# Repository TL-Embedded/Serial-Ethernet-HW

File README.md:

# Serial-Ethernet-HW

This is an Ethernet to Serial adaptor.
See [Serial-Ethernet-FW](https://github.com/TL-Embedded/Serial-Ethernet-FW) for the firmware project.

The hardware is done using KiCad, and uses my component library found here: [KiCadLib](https://github.com/Lambosaurus/KicadLib)

The processor is a STM32G061.

# Ethernet
The ethernet is managed by a SPI attached W5500. The ethernet is capable of 10/100 speeds.

# Serial
The serial is a TTL level serial targeted at certain test equipment. Series resistance is used to tolerate both 3V3 and 5V0 devices.

**This is not compatible with RS232 level serial**

# Power
The device is powered from 5V. This can be supplied via:
 * USB Connector
 * Debug connector
 * DB9 pin 1 (omit L2 if this is not desired)

# Debugging
The debugging connector is a TC2050 compatible footprint. See the [SWD-UART_CTX-10](https://github.com/TL-Embedded/SWD-UART-CTX-10) project for the adaptor board.

This can be used to:
 * Connect to the STM32 via STLINK
 * Supply 5V
 * Connect a UART

The debugging connector has no input/output protection - so take care not to supply power or UART when the DB9 is connected.

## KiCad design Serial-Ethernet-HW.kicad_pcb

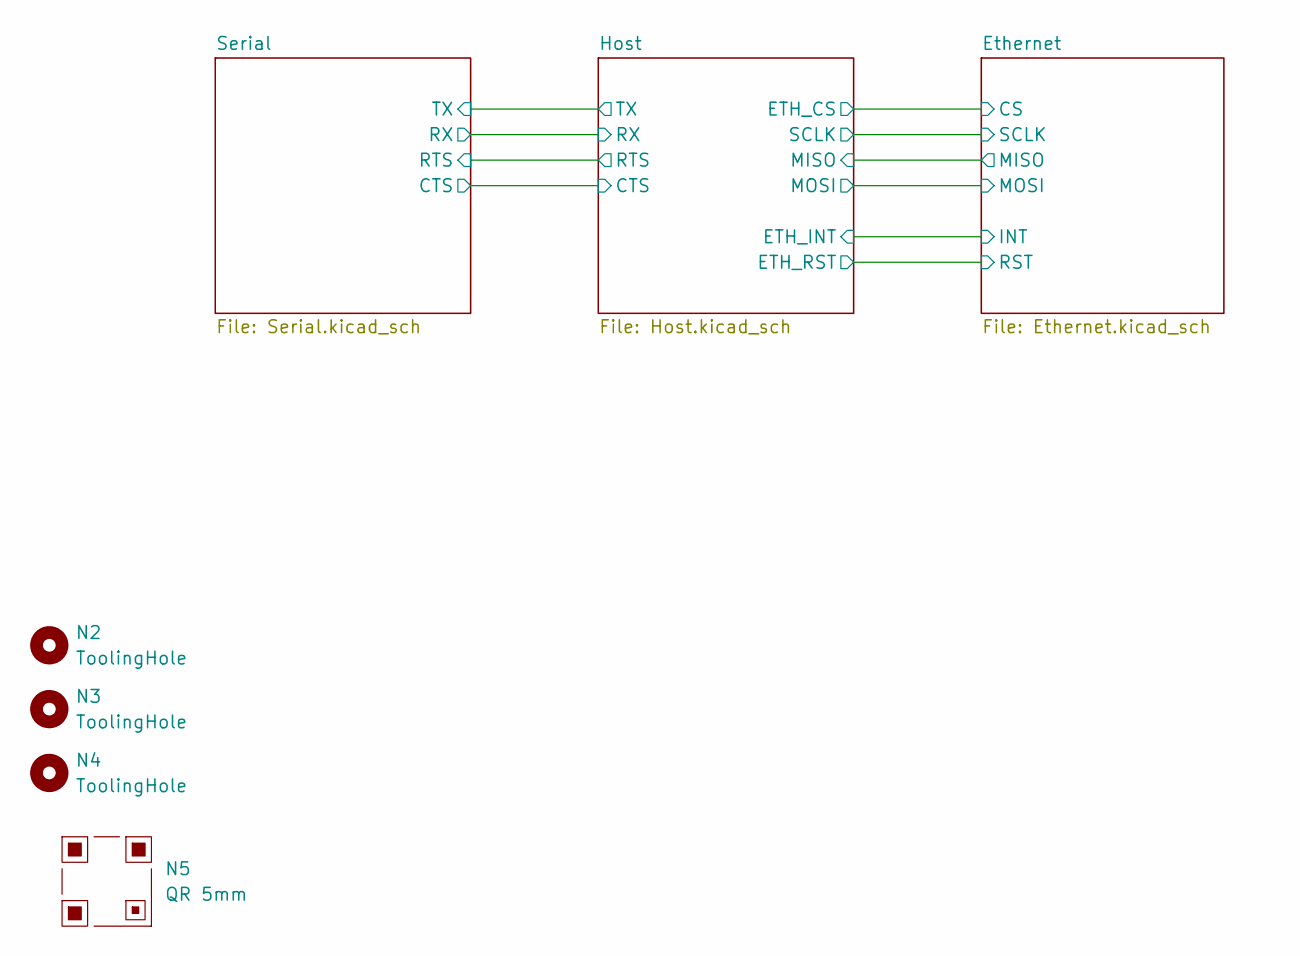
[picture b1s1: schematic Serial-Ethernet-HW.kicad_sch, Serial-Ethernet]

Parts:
N2, N3, N4: ToolingHole; ToolingHole_1mm
N5: QR 5mm; QR_5mm_JLC

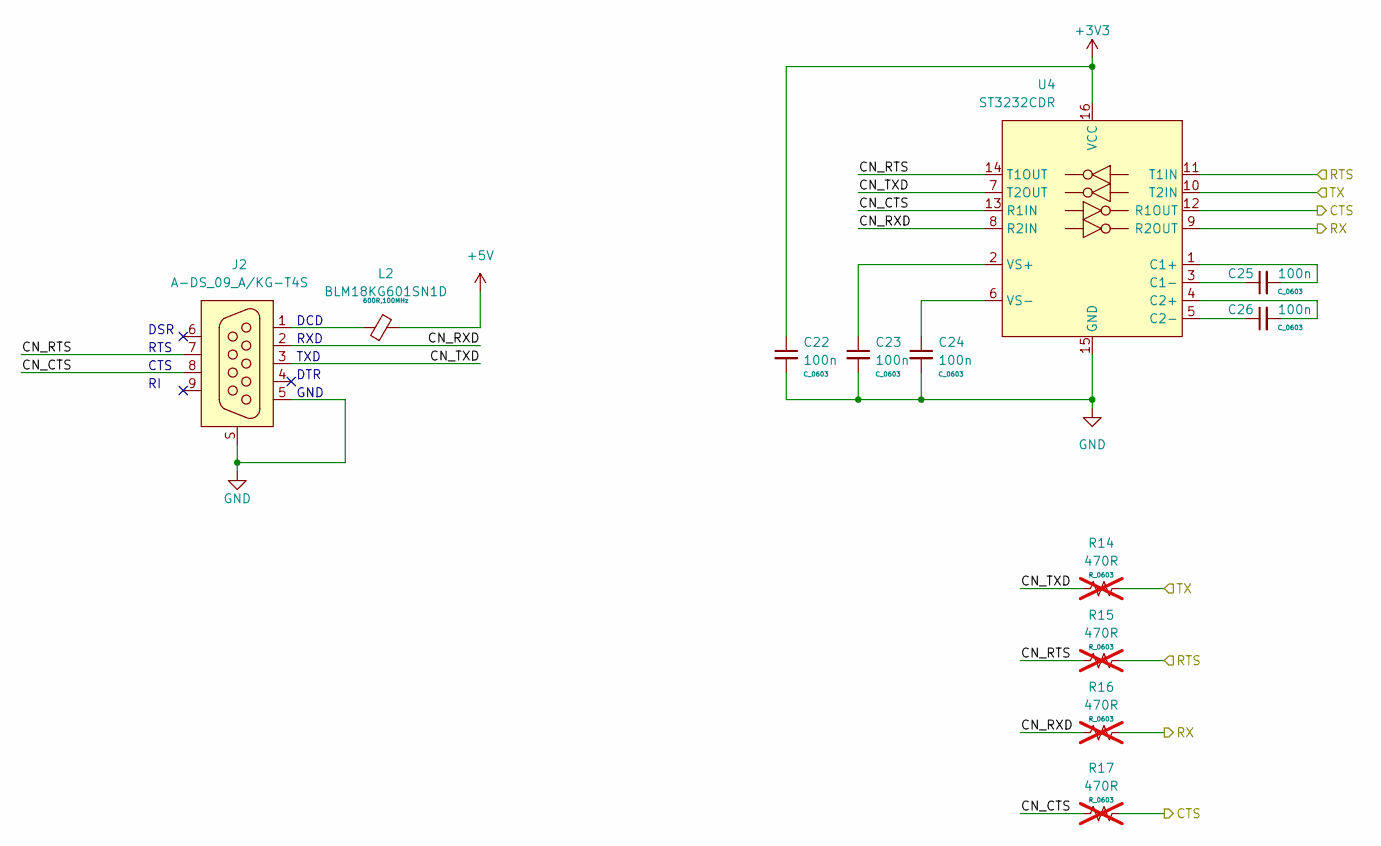
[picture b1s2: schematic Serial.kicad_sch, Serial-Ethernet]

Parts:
C22, C23, C24, C25, C26: 100n; C_0603
J2: A-DS_09_A/KG-T4S; DSUB09_Male_Horizontal
L2: BLM18KG601SN1D; FB_0603
R14, R15, R16, R17: 470R; R_0603; not fitted
U4: ST3232CDR; SOIC_16

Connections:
+3V3: C22.1, U4.16 (VCC); also elsewhere on the board
+5V: L2.2; also elsewhere on the board
/Host/CTS: R17.2, U4.12 (R1OUT); also elsewhere on the board
/Host/RTS: R15.2, U4.11 (T1IN); also elsewhere on the board
/Host/UART_RX: R16.2, U4.9 (R2OUT); also elsewhere on the board
/Host/UART_TX: R14.2, U4.10 (T2IN); also elsewhere on the board
/Serial/CN_CTS: J2.8, R17.1, U4.13 (R1IN)
/Serial/CN_RTS: J2.7, R15.1, U4.14 (T1OUT)
/Serial/CN_RXD: J2.2, R16.1, U4.8 (R2IN)
/Serial/CN_TXD: J2.3, R14.1, U4.7 (T2OUT)
GND: C22.2, C23.2, C24.2, J2.5, J2.S, U4.15 (GND); also elsewhere on the board
unnamed: J2.1, L2.1
unnamed: C25.2, U4.1 (C1+)
unnamed: C25.1, U4.3 (C1-)
unnamed: C26.2, U4.4 (C2+)
unnamed: C26.1, U4.5 (C2-)
unnamed: C23.1, U4.2 (VS+)
unnamed: C24.1, U4.6 (VS-)

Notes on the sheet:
GND
TXD
CTS
RXD
DTR
RTS
DSR
DCD

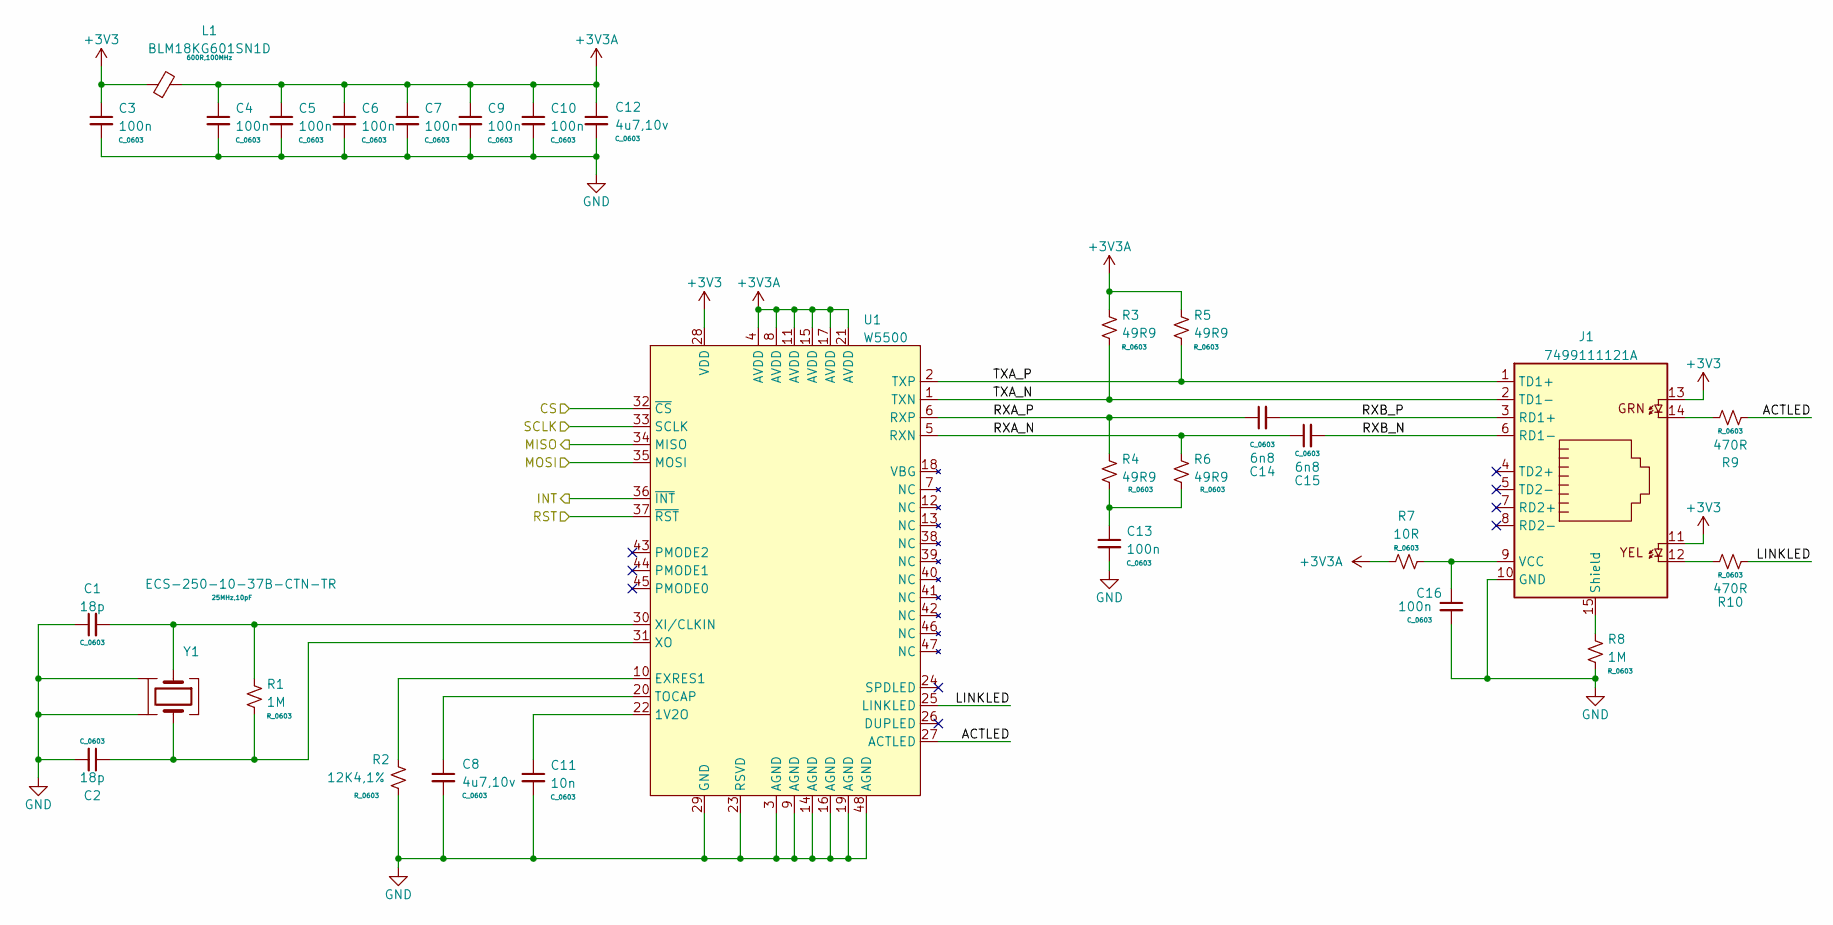
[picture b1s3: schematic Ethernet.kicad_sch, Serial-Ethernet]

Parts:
C1, C2: 18p; C_0603
C3, C4, C5, C6, C7, C9, C10, C13, C16: 100n; C_0603
C8, C12: 4u7,10v; C_0603
C11: 10n; C_0603
C14, C15: 6n8; C_0603
J1: 7499111121A; 7499210121A
L1: BLM18KG601SN1D; FB_0603
R1, R8: 1M; R_0603
R2: 12K4,1%; R_0603
R3, R4, R5, R6: 49R9; R_0603
R7: 10R; R_0603
R9, R10: 470R; R_0603
U1: W5500; LQFP48_05_7x7
Y1: ECS-250-10-37B-CTN-TR; Crystal_SMD4_2.0x1.6

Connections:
+3V3: C3.1, J1.11, J1.13, L1.1, U1.28 (VDD); also elsewhere on the board
+3V3A: C4.1, C5.1, C6.1, C7.1, C9.1, C10.1, C12.1, L1.2, R3.1, R5.1, R7.1, U1.4 (AVDD), U1.8 (AVDD), U1.11 (AVDD), U1.15 (AVDD), U1.17 (AVDD), U1.21 (AVDD)
/Ethernet/ACTLED: R9.1, U1.27 (ACTLED)
/Ethernet/CS: U1.32 (~CS); also elsewhere on the board
/Ethernet/INT: U1.36 (~INT); also elsewhere on the board
/Ethernet/LINKLED: R10.2, U1.25 (LINKLED)
/Ethernet/MISO: U1.34 (MISO); also elsewhere on the board
/Ethernet/MOSI: U1.35 (MOSI); also elsewhere on the board
/Ethernet/RST: U1.37 (~RST); also elsewhere on the board
/Ethernet/RXA_N: C15.1, R6.1, U1.5 (RXN)
/Ethernet/RXA_P: C14.1, R4.1, U1.6 (RXP)
/Ethernet/RXB_N: C15.2, J1.6 (RD1-)
/Ethernet/RXB_P: C14.2, J1.3 (RD1+)
/Ethernet/SCLK: U1.33 (SCLK); also elsewhere on the board
/Ethernet/TXA_N: J1.2 (TD1-), R3.2, U1.1 (TXN)
/Ethernet/TXA_P: J1.1 (TD1+), R5.2, U1.2 (TXP)
GND: C1.1, C2.2, C3.2, C4.2, C5.2, C6.2, C7.2, C8.2, C9.2, C10.2, C11.2, C12.2, C13.2, C16.2, J1.10 (GND), R2.2, R8.2, U1.3 (AGND), U1.9 (AGND), U1.14 (AGND), U1.16 (AGND), U1.19 (AGND), U1.23 (RSVD), U1.29 (GND), U1.48 (AGND), Y1.2, Y1.4; also elsewhere on the board
unnamed: C13.1, R4.2, R6.2
unnamed: J1.12, R10.1
unnamed: J1.14, R9.2
unnamed: J1.15 (Shield), R8.1
unnamed: C16.1, J1.9 (VCC), R7.2
unnamed: C11.1, U1.22 (1V2O)
unnamed: R2.1, U1.10 (EXRES1)
unnamed: C8.1, U1.20 (TOCAP)
unnamed: C1.2, R1.1, U1.30 (XI/CLKIN), Y1.1
unnamed: C2.1, R1.2, U1.31 (XO), Y1.3

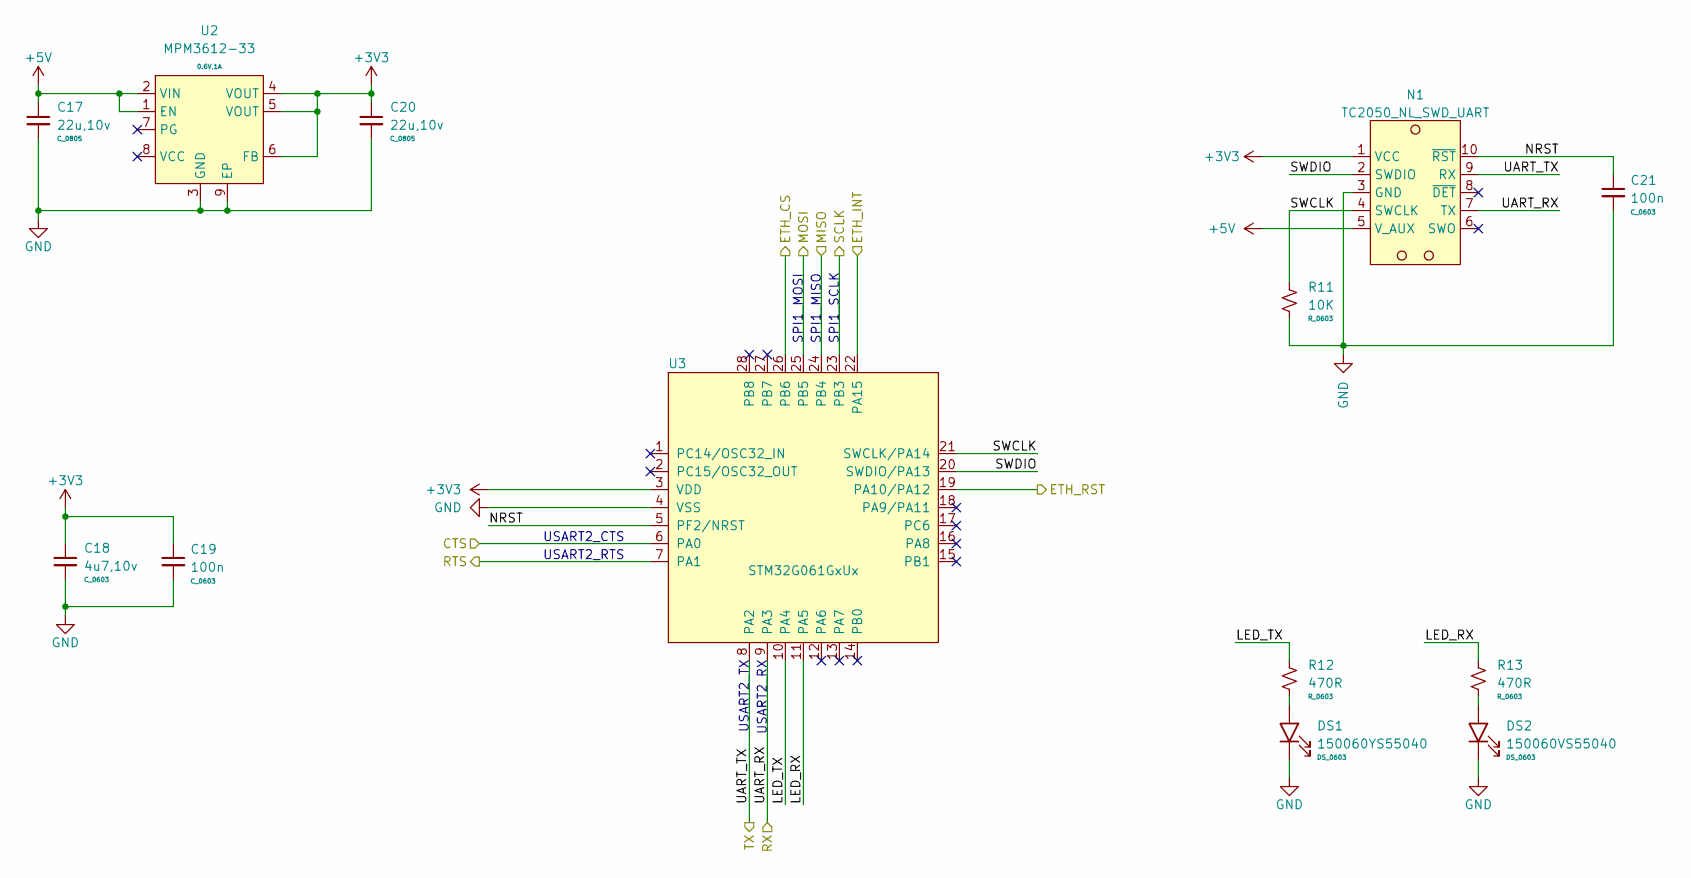
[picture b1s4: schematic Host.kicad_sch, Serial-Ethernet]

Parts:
C17, C20: 22u,10v; C_0805
C18: 4u7,10v; C_0603
C19, C21: 100n; C_0603
DS1: 150060YS55040; DS_0603
DS2: 150060VS55040; DS_0603
N1: TC2050_NL_SWD_UART; TagConnect_TC2050_NL
R11: 10K; R_0603
R12, R13: 470R; R_0603
U2: MPM3612-33; LGA8_3x3_EP_MPM
U3: STM32G061GxUx; QFN28_05_4x4

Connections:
+3V3: C18.1, C19.1, C20.1, N1.1 (VCC), U2.4 (VOUT), U2.5 (VOUT), U2.6 (FB), U3.3 (VDD); also elsewhere on the board
+5V: C17.1, N1.5 (V_AUX), U2.1 (EN), U2.2 (VIN); also elsewhere on the board
/Ethernet/CS: U3.26 (PB6); also elsewhere on the board
/Ethernet/INT: U3.22 (PA15); also elsewhere on the board
/Ethernet/MISO: U3.24 (PB4); also elsewhere on the board
/Ethernet/MOSI: U3.25 (PB5); also elsewhere on the board
/Ethernet/RST: U3.19 (PA10/PA12); also elsewhere on the board
/Ethernet/SCLK: U3.23 (PB3); also elsewhere on the board
/Host/CTS: U3.6 (PA0); also elsewhere on the board
/Host/LED_RX: R13.1, U3.11 (PA5)
/Host/LED_TX: R12.1, U3.10 (PA4)
/Host/NRST: C21.1, N1.10 (~RST), U3.5 (PF2/NRST)
/Host/RTS: U3.7 (PA1); also elsewhere on the board
/Host/SWCLK: N1.4 (SWCLK), R11.1, U3.21 (SWCLK/PA14)
/Host/SWDIO: N1.2 (SWDIO), U3.20 (SWDIO/PA13)
/Host/UART_RX: N1.7 (TX), U3.9 (PA3); also elsewhere on the board
/Host/UART_TX: N1.9 (RX), U3.8 (PA2); also elsewhere on the board
GND: C17.2, C18.2, C19.2, C20.2, C21.2, DS1.1 (K), DS2.1 (K), N1.3 (GND), R11.2, U2.3 (GND), U2.9 (EP), U3.4 (VSS); also elsewhere on the board
unnamed: DS1.2 (A), R12.2
unnamed: DS2.2 (A), R13.2

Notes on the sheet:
SPI1_SCLK
SPI1_MOSI
SPI1_MISO
USART2_RTS
USART2_RX
USART2_CTS
USART2_TX

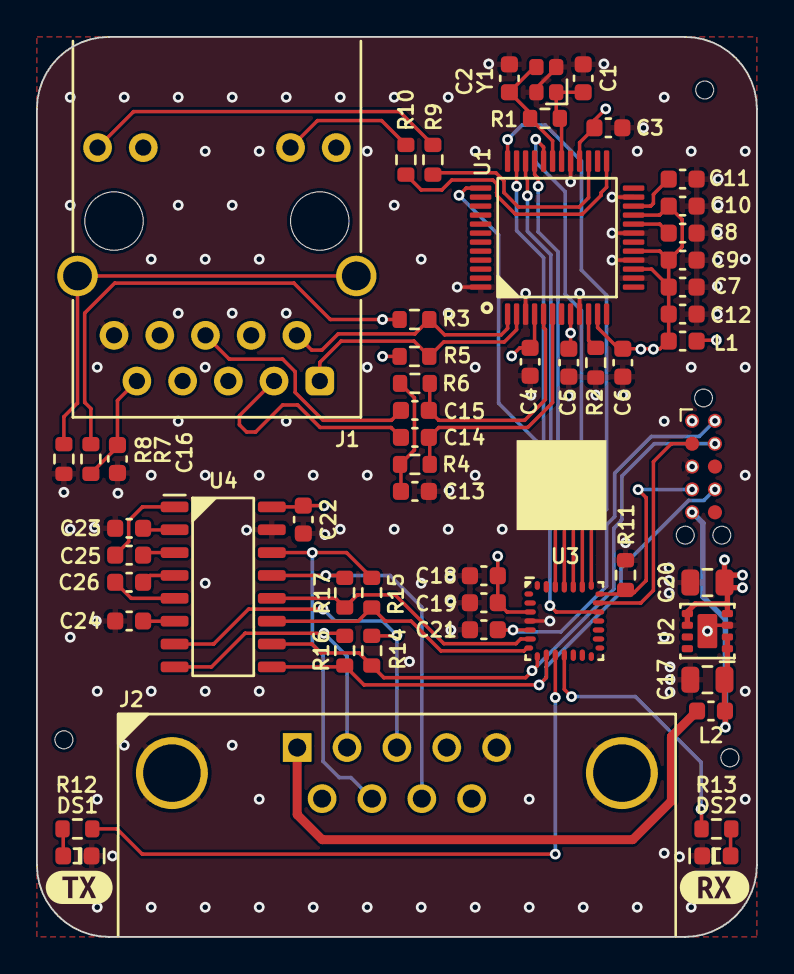
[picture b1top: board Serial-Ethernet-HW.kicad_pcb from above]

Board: 4 copper layers, 40.0 x 50.0 mm, 61 parts (0 on the bottom side), 50 nets.

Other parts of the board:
kibuzzard-6A8D4FDF: G***; kibuzzard-6A8D4FDF
kibuzzard-6A8D4FE5: G***; kibuzzard-6A8D4FE5

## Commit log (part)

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2023-02-09 Version 1.0
2023-04-18 Reference kicad lib in readme
2025-09-13 Rebuild using new output scripts
